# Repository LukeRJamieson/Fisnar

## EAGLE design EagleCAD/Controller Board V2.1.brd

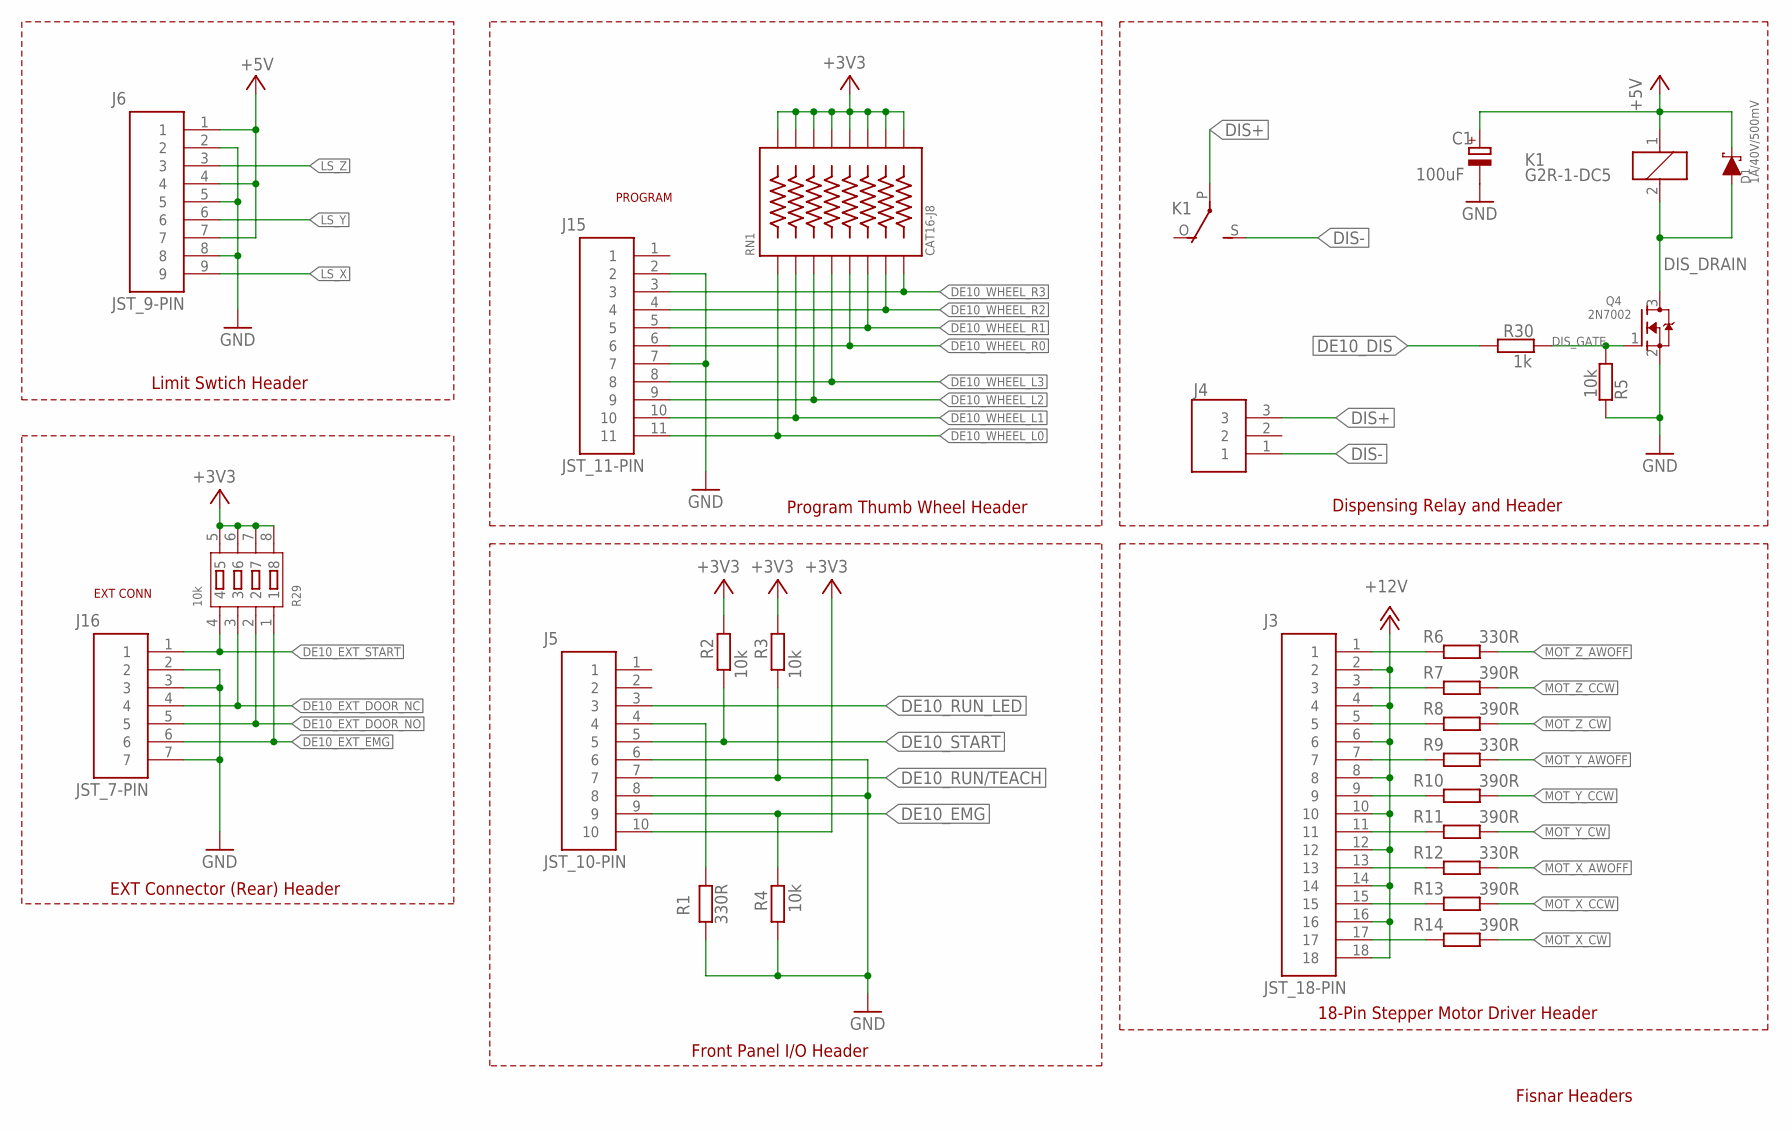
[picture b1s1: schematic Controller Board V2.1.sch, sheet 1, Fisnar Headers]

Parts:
C1: 100uF; 153CLV-0810
D1: 1A/40V/500mV; SMA-DIODE
J3: JST_18-PIN
J4: JST_3-PIN
J5: JST_10-PIN
J6: JST_9-PIN
J15: JST_11-PIN
J16: JST_7-PIN
K1: G2R-1-DC5; G2R
Q4: 2N7002; SOT23
R1, R6, R9, R12: 330R; R0805
R2, R3, R4, R5: 10k; R0805
R7, R8, R10, R11, R13, R14: 390R; R0805
R29: 10k; RA1206-8
R30: 1k; R0805
RN1: CAT16-J8; RN8

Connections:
+3V3: J5.10, R2.2, R3.2, R29.5, R29.6, R29.7, R29.8, RN1.2, RN1.4, RN1.6, RN1.8, RN1.10, RN1.12, RN1.14, RN1.16; also elsewhere on the board
+5V: C1.+, D1.C, J6.1, J6.4, J6.7, K1.1; also elsewhere on the board
+12V: J3.2, J3.4, J3.6, J3.8, J3.10, J3.12, J3.14, J3.16, J3.18; also elsewhere on the board
DE10_DIS: R30.2; also elsewhere on the board
DE10_EMG: J5.9, R4.2; also elsewhere on the board
DE10_EXT_DOOR_NC: J16.4, R29.3; also elsewhere on the board
DE10_EXT_DOOR_NO: J16.5, R29.2; also elsewhere on the board
DE10_EXT_EMG: J16.6, R29.1; also elsewhere on the board
DE10_EXT_START: J16.1, R29.4; also elsewhere on the board
DE10_RUN/TEACH: J5.7, R3.1; also elsewhere on the board
DE10_RUN_LED: J5.3; also elsewhere on the board
DE10_START: J5.5, R2.1; also elsewhere on the board
DE10_WHEEL_L0: J15.11, RN1.1; also elsewhere on the board
DE10_WHEEL_L1: J15.10, RN1.3; also elsewhere on the board
DE10_WHEEL_L2: J15.9, RN1.5; also elsewhere on the board
DE10_WHEEL_L3: J15.8, RN1.7; also elsewhere on the board
DE10_WHEEL_R0: J15.6, RN1.9; also elsewhere on the board
DE10_WHEEL_R1: J15.5, RN1.11; also elsewhere on the board
DE10_WHEEL_R2: J15.4, RN1.13; also elsewhere on the board
DE10_WHEEL_R3: J15.3, RN1.15; also elsewhere on the board
DIS+: J4.3, K1.P
DIS-: J4.1, K1.S
DIS_DRAIN: D1.A, K1.2, Q4.3 (D)
DIS_GATE: Q4.1 (G), R5.2, R30.1
GND: C1.-, J5.6, J5.8, J6.2, J6.5, J6.8, J15.2, J15.7, J16.2, J16.3, J16.7, Q4.2 (S), R1.2, R4.1, R5.1; also elsewhere on the board
LS_X: J6.9; also elsewhere on the board
LS_Y: J6.6; also elsewhere on the board
LS_Z: J6.3; also elsewhere on the board
MOT_X_AWOFF: R12.1; also elsewhere on the board
MOT_X_CCW: R13.1; also elsewhere on the board
MOT_X_CW: R14.1; also elsewhere on the board
MOT_Y_AWOFF: R9.1; also elsewhere on the board
MOT_Y_CCW: R10.1; also elsewhere on the board
MOT_Y_CW: R11.1; also elsewhere on the board
MOT_Z_AWOFF: R6.1; also elsewhere on the board
MOT_Z_CCW: R7.1; also elsewhere on the board
MOT_Z_CW: R8.1; also elsewhere on the board
RUN_LED_RES: J5.4, R1.1
X_AWOFF_NEG: J3.13, R12.2
X_CCW_NEG: J3.15, R13.2
X_CW_NEG: J3.17, R14.2
Y_AWOFF_NEG: J3.7, R9.2
Y_CCW_NEG: J3.9, R10.2
Y_CW_NEG: J3.11, R11.2
Z_AWOFF_NEG: J3.1, R6.2
Z_CCW_NEG: J3.3, R7.2
Z_CW_NEG: J3.5, R8.2

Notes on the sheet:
Fisnar Headers
EXT CONN
PROGRAM
18-Pin Stepper Motor Driver Header
Front Panel I/O Header
EXT Connector (Rear) Header
Limit Swtich Header
Program Thumb Wheel Header
Dispensing Relay and Header

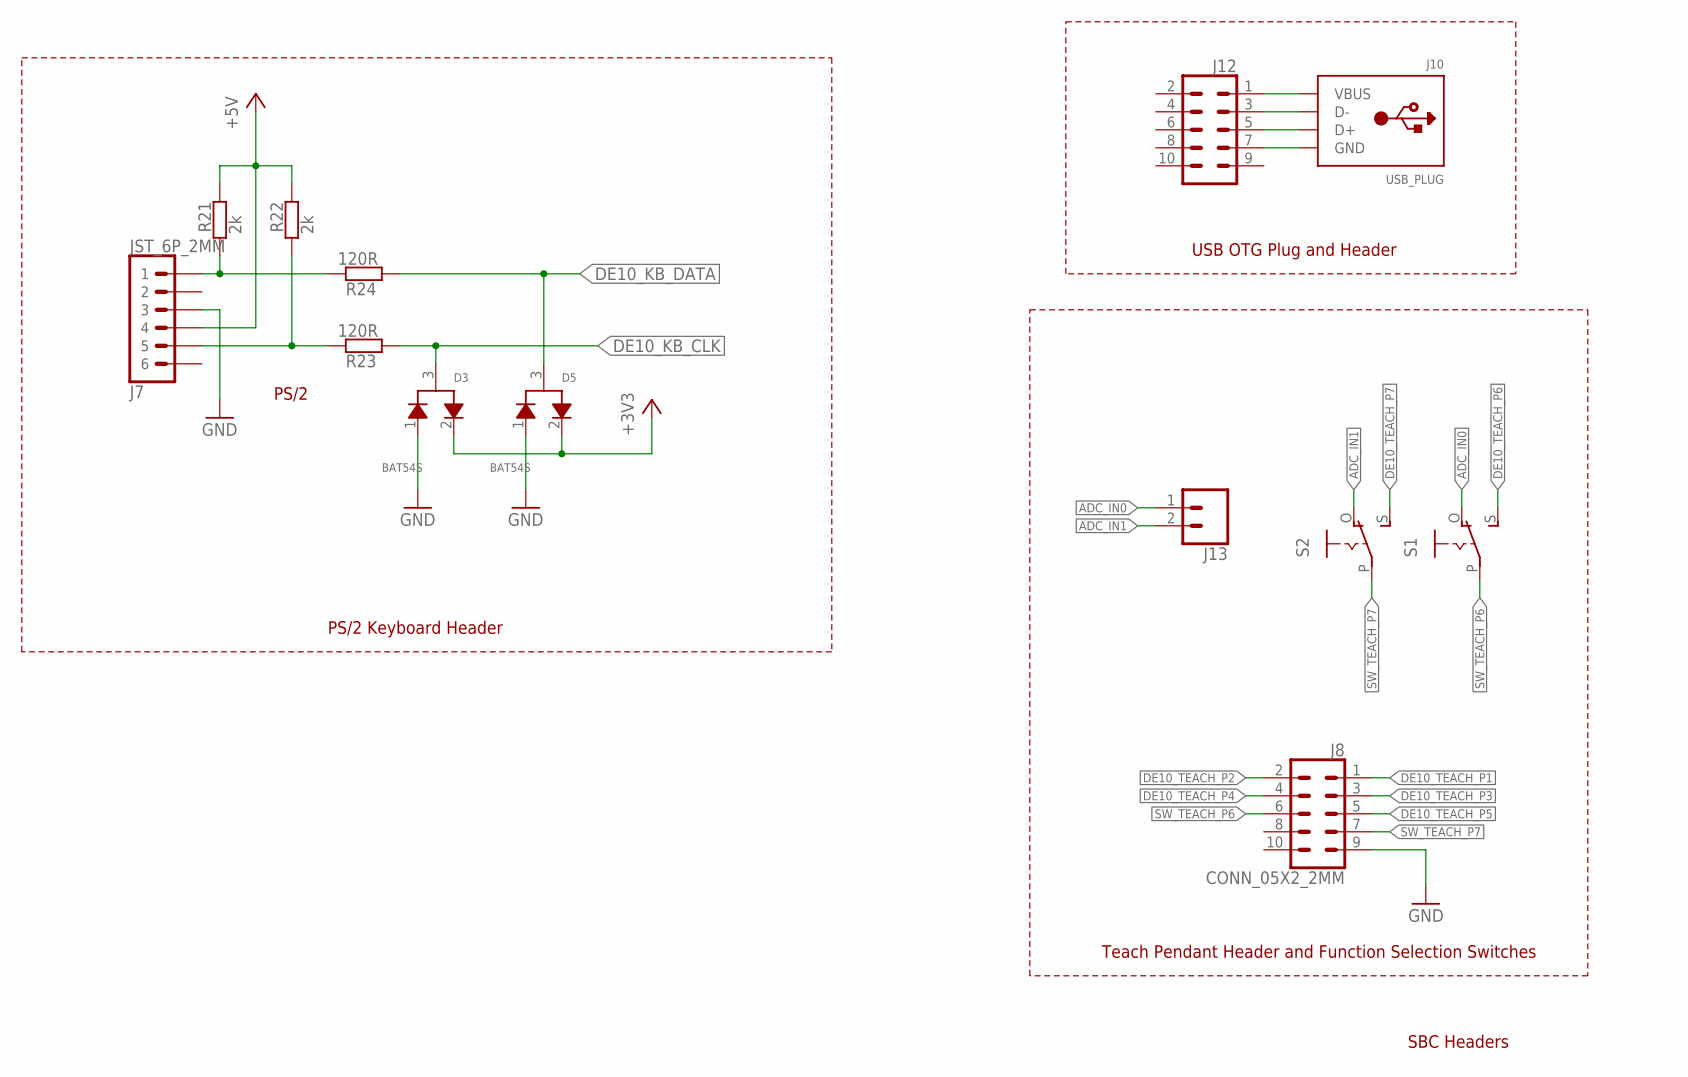
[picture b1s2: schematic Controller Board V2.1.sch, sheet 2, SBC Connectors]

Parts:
D3, D5: BAT54S; SOT23
J7: JST_6P_2MM
J8: CONN_05X2_2MM; 2X5-SHROUDED-2MM
J10: USB_PLUG
J12: CONN_05X2PTH; 2X5
J13: CONN_02; 1X02
R21, R22: 2k; R0805
R23, R24: 120R; R0805
S1, S2: EG1218S; EG1218

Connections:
+3V3: D3.2, D5.2; also elsewhere on the board
+5V: J7.P$4 (4), R21.2, R22.2; also elsewhere on the board
ADC_IN0: J13.1, S1.O
ADC_IN1: J13.2, S2.O
DE10_KB_CLK: D3.3, R23.1; also elsewhere on the board
DE10_KB_DATA: D5.3, R24.1; also elsewhere on the board
DE10_TEACH_P1: J8.1; also elsewhere on the board
DE10_TEACH_P2: J8.2; also elsewhere on the board
DE10_TEACH_P3: J8.3; also elsewhere on the board
DE10_TEACH_P4: J8.4; also elsewhere on the board
DE10_TEACH_P5: J8.5; also elsewhere on the board
DE10_TEACH_P6: S1.S; also elsewhere on the board
DE10_TEACH_P7: S2.S; also elsewhere on the board
GND: D3.1, D5.1, J7.P$3 (3), J8.9; also elsewhere on the board
OTG_D+: J10.D+, J12.5
OTG_D-: J10.D-, J12.3
OTG_GND: J10.USB_GND (GND), J12.7
OTG_VBUS: J10.VBUS, J12.1
PS2_KB_CLK: J7.P$5 (5), R22.1, R23.2
PS2_KB_DATA: J7.P$1 (1), R21.1, R24.2
SW_TEACH_P6: J8.6, S1.P
SW_TEACH_P7: J8.7, S2.P

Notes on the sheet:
PS/2
SBC Headers
PS/2 Keyboard Header
USB OTG Plug and Header
Teach Pendant Header and Function Selection Switches

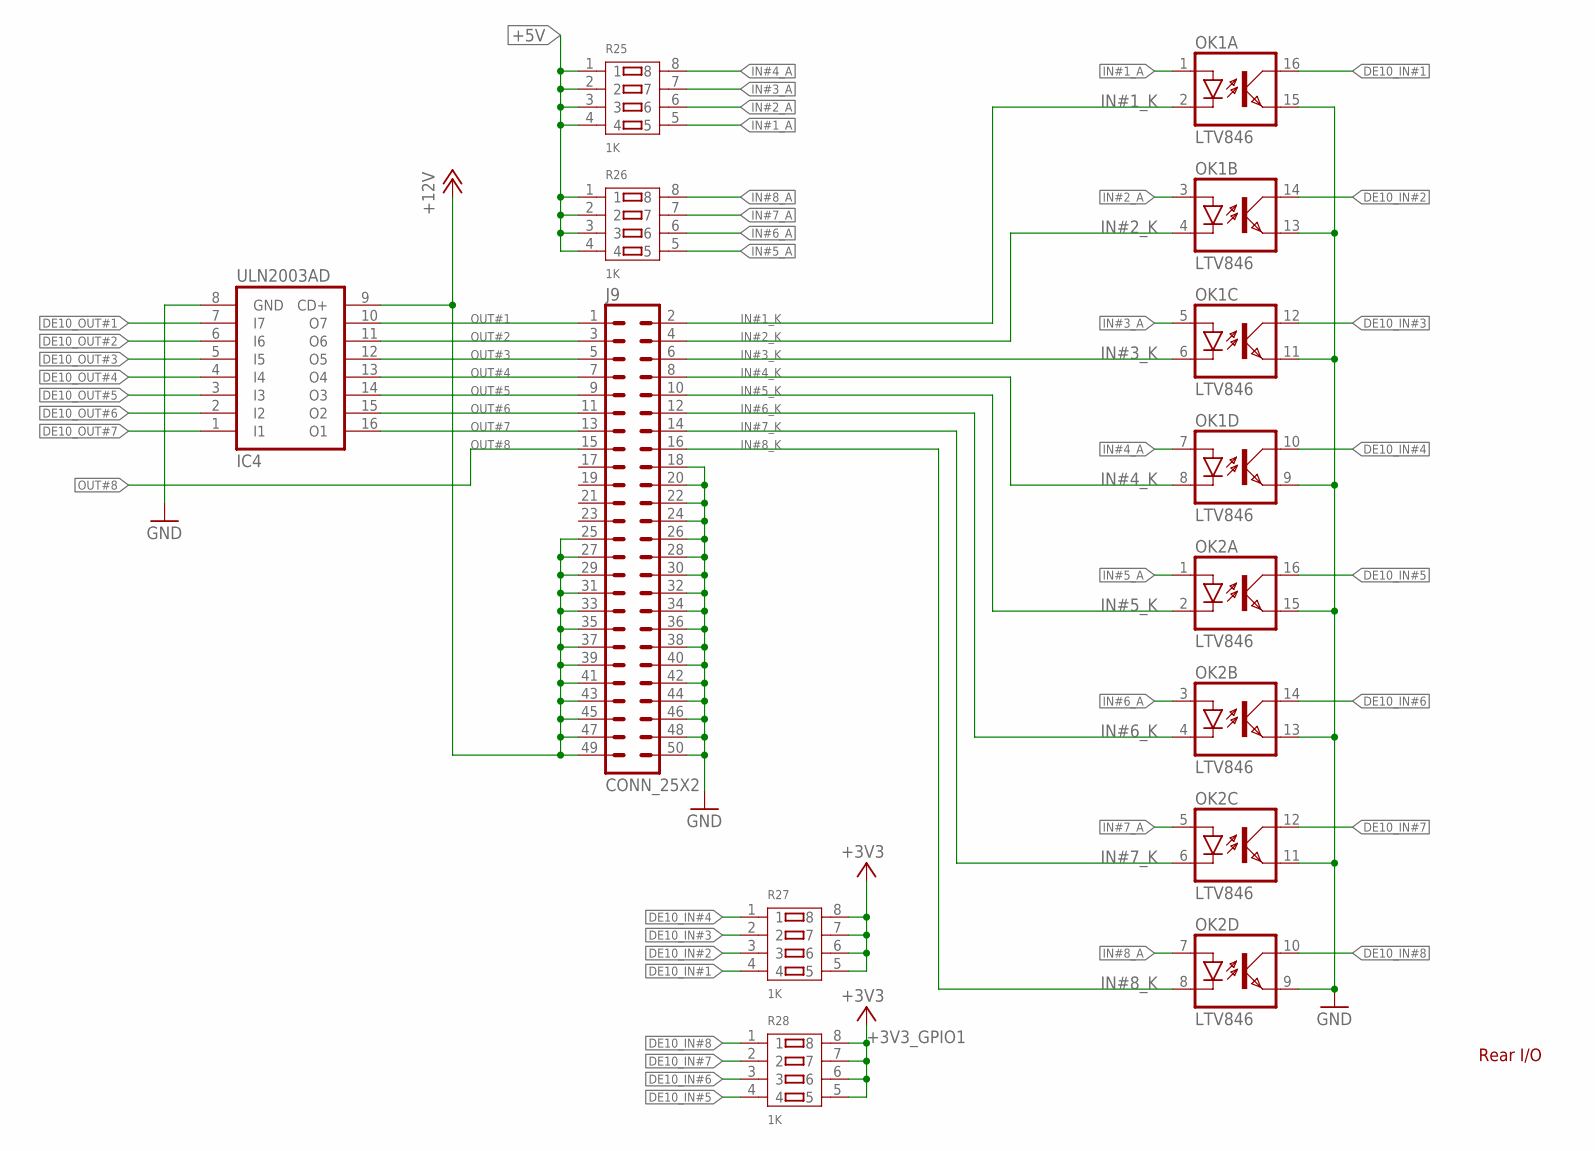
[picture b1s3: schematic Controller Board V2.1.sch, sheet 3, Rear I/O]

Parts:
IC4: ULN2003AD; SO16
J9: CONN_25X2; 2X25
OK1, OK2: LTV846; DIL8-SMD
R25, R26, R27, R28: 1K; RA1206-8

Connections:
+3V3: R27.5, R27.6, R27.7, R27.8; also elsewhere on the board
+3V3_GPIO1: R28.5, R28.6, R28.7, R28.8; also elsewhere on the board
+5V: R25.1, R25.2, R25.3, R25.4, R26.1, R26.2, R26.3, R26.4; also elsewhere on the board
+12V: IC4.9 (CD+), J9.25, J9.27, J9.29, J9.31, J9.33, J9.35, J9.37, J9.39, J9.41, J9.43, J9.45, J9.47, J9.49; also elsewhere on the board
DE10_IN#1: OK1.16 (COL), R27.4; also elsewhere on the board
DE10_IN#2: OK1.14 (COL), R27.3; also elsewhere on the board
DE10_IN#3: OK1.12 (COL), R27.2; also elsewhere on the board
DE10_IN#4: OK1.10 (COL), R27.1; also elsewhere on the board
DE10_IN#5: OK2.16 (COL), R28.4; also elsewhere on the board
DE10_IN#6: OK2.14 (COL), R28.3; also elsewhere on the board
DE10_IN#7: OK2.12 (COL), R28.2; also elsewhere on the board
DE10_IN#8: OK2.10 (COL), R28.1; also elsewhere on the board
DE10_OUT#1: IC4.7 (I7); also elsewhere on the board
DE10_OUT#2: IC4.6 (I6); also elsewhere on the board
DE10_OUT#3: IC4.5 (I5); also elsewhere on the board
DE10_OUT#4: IC4.4 (I4); also elsewhere on the board
DE10_OUT#5: IC4.3 (I3); also elsewhere on the board
DE10_OUT#6: IC4.2 (I2); also elsewhere on the board
DE10_OUT#7: IC4.1 (I1); also elsewhere on the board
GND: IC4.8 (GND), J9.18, J9.20, J9.22, J9.24, J9.26, J9.28, J9.30, J9.32, J9.34, J9.36, J9.38, J9.40, J9.42, J9.44, J9.46, J9.48, J9.50, OK1.9 (EMIT), OK1.11 (EMIT), OK1.13 (EMIT), OK1.15 (EMIT), OK2.9 (EMIT), OK2.11 (EMIT), OK2.13 (EMIT), OK2.15 (EMIT); also elsewhere on the board
IN#1_A: OK1.1 (A), R25.5
IN#1_K: J9.2, OK1.2 (C)
IN#2_A: OK1.3 (A), R25.6
IN#2_K: J9.4, OK1.4 (C)
IN#3_A: OK1.5 (A), R25.7
IN#3_K: J9.6, OK1.6 (C)
IN#4_A: OK1.7 (A), R25.8
IN#4_K: J9.8, OK1.8 (C)
IN#5_A: OK2.1 (A), R26.5
IN#5_K: J9.10, OK2.2 (C)
IN#6_A: OK2.3 (A), R26.6
IN#6_K: J9.12, OK2.4 (C)
IN#7_A: OK2.5 (A), R26.7
IN#7_K: J9.14, OK2.6 (C)
IN#8_A: OK2.7 (A), R26.8
IN#8_K: J9.16, OK2.8 (C)
OUT#1: IC4.10 (O7), J9.1
OUT#2: IC4.11 (O6), J9.3
OUT#3: IC4.12 (O5), J9.5
OUT#4: IC4.13 (O4), J9.7
OUT#5: IC4.14 (O3), J9.9
OUT#6: IC4.15 (O2), J9.11
OUT#7: IC4.16 (O1), J9.13
OUT#8: J9.15; also elsewhere on the board

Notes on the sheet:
Rear I/O

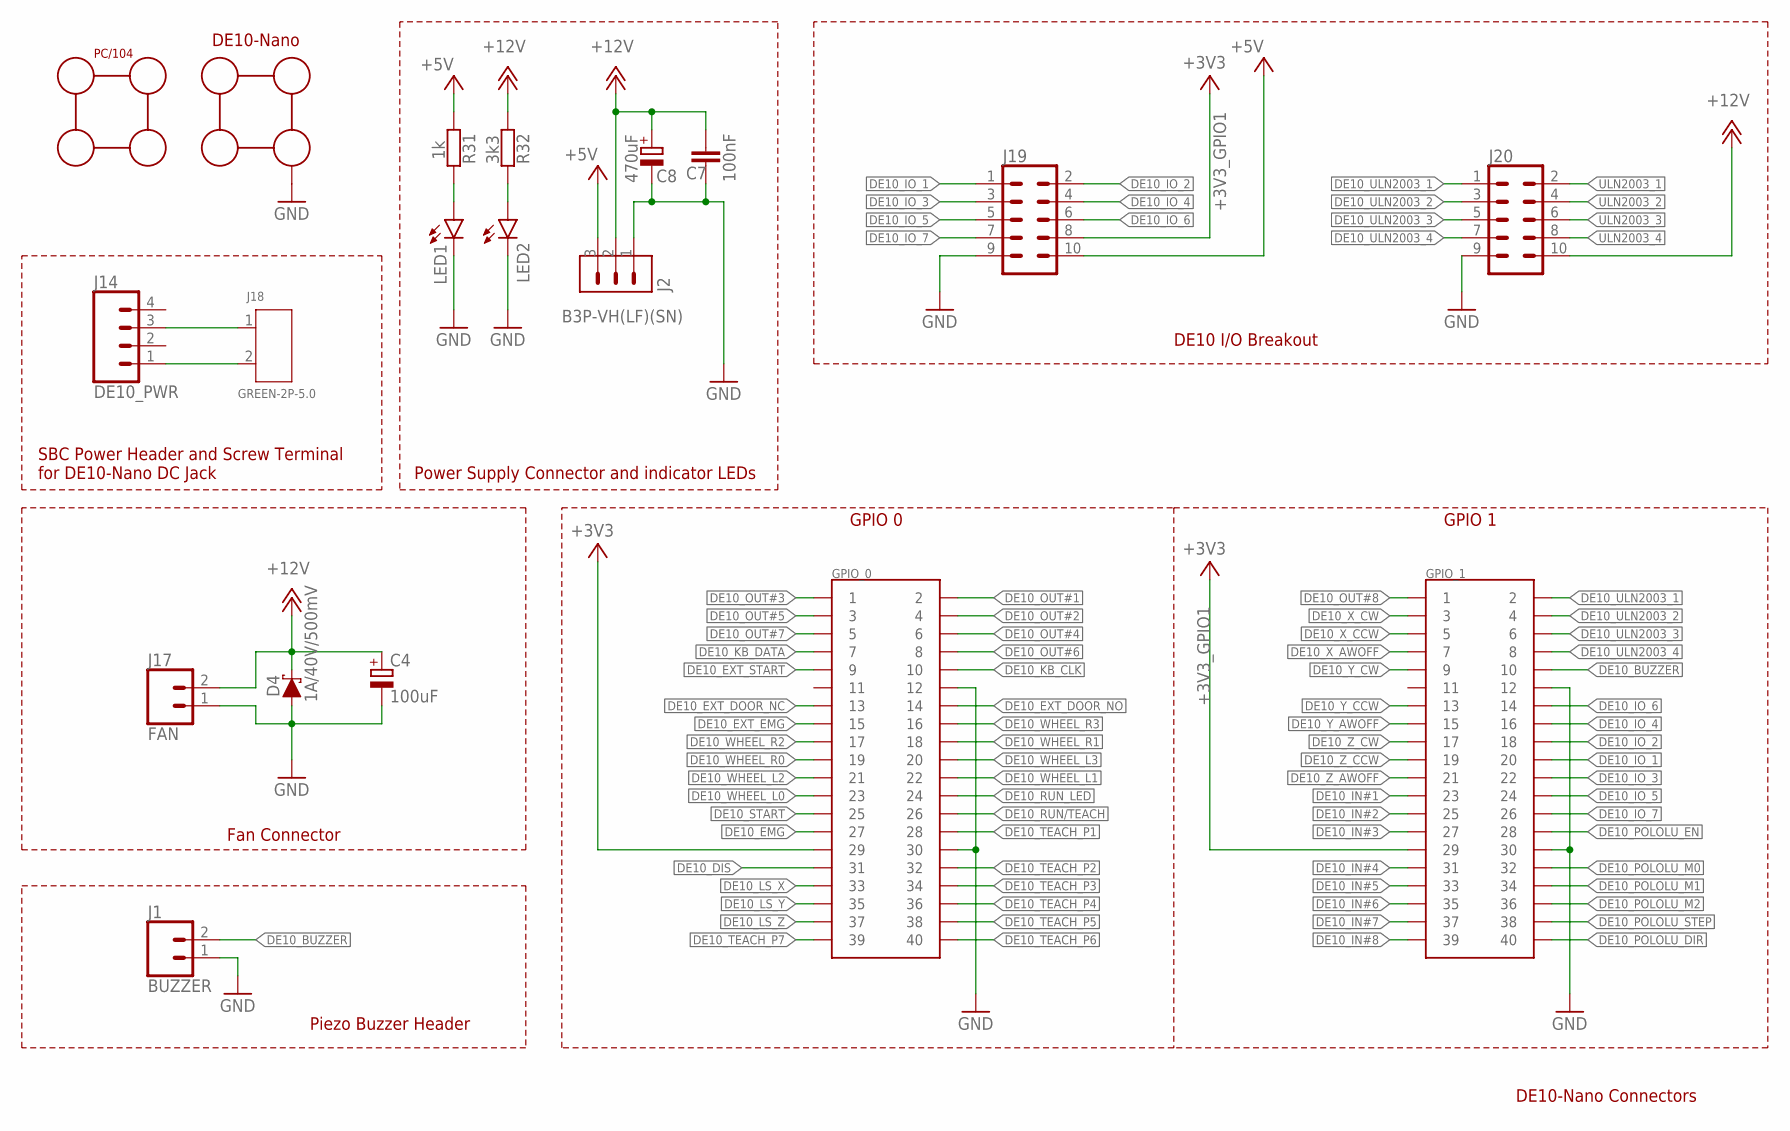
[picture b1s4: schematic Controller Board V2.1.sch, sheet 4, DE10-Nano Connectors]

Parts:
C4: 100uF; 153CLV-0810
C7: 100nF; C0805
C8: 470uF; 153CLV-0810
D4: 1A/40V/500mV; SMA-DIODE
DE1: DE10_FOOTPRINT
J1: BUZZER; 1X02
J2: B3P-VH(LF)(SN); HDR-03
J14: DE10_PWR; 1X04_NO_SILK
J17: FAN; 1X02
J18: GREEN-2P-5.0; H2-5.0-10.5X8.0MM
J19, J20: CONN_05X2PTH; 2X5
LED1, LED2: LEDCHIP-LED0805; CHIP-LED0805
R31: 1k; R0805
R32: 3k3; R0805
U$1: PC104_FOOTPRINT

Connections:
+3V3: DE1.GPIO_0_29 (29); also elsewhere on the board
+3V3_GPIO1: DE1.GPIO_1_29 (29), J19.8; also elsewhere on the board
+5V: J2.3, J19.10, R31.1; also elsewhere on the board
+12V: C4.+, C7.1, C8.+, D4.C, J2.2, J17.2, J20.10, R32.1; also elsewhere on the board
DE10_BUZZER: DE1.GPIO_1_10 (10), J1.2
DE10_DCJACK_5V: J14.1, J18.2
DE10_DCJACK_GND: J14.3, J18.1
DE10_DIS: DE1.GPIO_0_31 (31); also elsewhere on the board
DE10_EMG: DE1.GPIO_0_27 (27); also elsewhere on the board
DE10_EXT_DOOR_NC: DE1.GPIO_0_13 (13); also elsewhere on the board
DE10_EXT_DOOR_NO: DE1.GPIO_0_14 (14); also elsewhere on the board
DE10_EXT_EMG: DE1.GPIO_0_15 (15); also elsewhere on the board
DE10_EXT_START: DE1.GPIO_0_9 (9); also elsewhere on the board
DE10_IN#1: DE1.GPIO_1_23 (23); also elsewhere on the board
DE10_IN#2: DE1.GPIO_1_25 (25); also elsewhere on the board
DE10_IN#3: DE1.GPIO_1_27 (27); also elsewhere on the board
DE10_IN#4: DE1.GPIO_1_31 (31); also elsewhere on the board
DE10_IN#5: DE1.GPIO_1_33 (33); also elsewhere on the board
DE10_IN#6: DE1.GPIO_1_35 (35); also elsewhere on the board
DE10_IN#7: DE1.GPIO_1_37 (37); also elsewhere on the board
DE10_IN#8: DE1.GPIO_1_39 (39); also elsewhere on the board
DE10_IO_1: DE1.GPIO_1_20 (20), J19.1
DE10_IO_2: DE1.GPIO_1_18 (18), J19.2
DE10_IO_3: DE1.GPIO_1_22 (22), J19.3
DE10_IO_4: DE1.GPIO_1_16 (16), J19.4
DE10_IO_5: DE1.GPIO_1_24 (24), J19.5
DE10_IO_6: DE1.GPIO_1_14 (14), J19.6
DE10_IO_7: DE1.GPIO_1_26 (26), J19.7
DE10_KB_CLK: DE1.GPIO_0_10 (10); also elsewhere on the board
DE10_KB_DATA: DE1.GPIO_0_7 (7); also elsewhere on the board
DE10_LS_X: DE1.GPIO_0_33 (33); also elsewhere on the board
DE10_LS_Y: DE1.GPIO_0_35 (35); also elsewhere on the board
DE10_LS_Z: DE1.GPIO_0_37 (37); also elsewhere on the board
DE10_OUT#1: DE1.GPIO_0_2 (2); also elsewhere on the board
DE10_OUT#2: DE1.GPIO_0_4 (4); also elsewhere on the board
DE10_OUT#3: DE1.GPIO_0_1 (1); also elsewhere on the board
DE10_OUT#4: DE1.GPIO_0_6 (6); also elsewhere on the board
DE10_OUT#5: DE1.GPIO_0_3 (3); also elsewhere on the board
DE10_OUT#6: DE1.GPIO_0_8 (8); also elsewhere on the board
DE10_OUT#7: DE1.GPIO_0_5 (5); also elsewhere on the board
DE10_OUT#8: DE1.GPIO_1_1 (1); also elsewhere on the board
DE10_POLOLU_DIR: DE1.GPIO_1_40 (40); also elsewhere on the board
DE10_POLOLU_EN: DE1.GPIO_1_28 (28); also elsewhere on the board
DE10_POLOLU_M0: DE1.GPIO_1_32 (32); also elsewhere on the board
DE10_POLOLU_M1: DE1.GPIO_1_34 (34); also elsewhere on the board
DE10_POLOLU_M2: DE1.GPIO_1_36 (36); also elsewhere on the board
DE10_POLOLU_STEP: DE1.GPIO_1_38 (38); also elsewhere on the board
DE10_RUN/TEACH: DE1.GPIO_0_26 (26); also elsewhere on the board
DE10_RUN_LED: DE1.GPIO_0_24 (24); also elsewhere on the board
DE10_START: DE1.GPIO_0_25 (25); also elsewhere on the board
DE10_TEACH_P1: DE1.GPIO_0_28 (28); also elsewhere on the board
DE10_TEACH_P2: DE1.GPIO_0_32 (32); also elsewhere on the board
DE10_TEACH_P3: DE1.GPIO_0_34 (34); also elsewhere on the board
DE10_TEACH_P4: DE1.GPIO_0_36 (36); also elsewhere on the board
DE10_TEACH_P5: DE1.GPIO_0_38 (38); also elsewhere on the board
DE10_TEACH_P6: DE1.GPIO_0_40 (40); also elsewhere on the board
DE10_TEACH_P7: DE1.GPIO_0_39 (39); also elsewhere on the board
DE10_ULN2003_1: DE1.GPIO_1_2 (2), J20.1; also elsewhere on the board
DE10_ULN2003_2: DE1.GPIO_1_4 (4), J20.3; also elsewhere on the board
DE10_ULN2003_3: DE1.GPIO_1_6 (6), J20.5; also elsewhere on the board
DE10_ULN2003_4: DE1.GPIO_1_8 (8), J20.7; also elsewhere on the board
DE10_WHEEL_L0: DE1.GPIO_0_23 (23); also elsewhere on the board
DE10_WHEEL_L1: DE1.GPIO_0_22 (22); also elsewhere on the board
DE10_WHEEL_L2: DE1.GPIO_0_21 (21); also elsewhere on the board
DE10_WHEEL_L3: DE1.GPIO_0_20 (20); also elsewhere on the board
DE10_WHEEL_R0: DE1.GPIO_0_19 (19); also elsewhere on the board
DE10_WHEEL_R1: DE1.GPIO_0_18 (18); also elsewhere on the board
DE10_WHEEL_R2: DE1.GPIO_0_17 (17); also elsewhere on the board
DE10_WHEEL_R3: DE1.GPIO_0_16 (16); also elsewhere on the board
DE10_X_AWOFF: DE1.GPIO_1_7 (7); also elsewhere on the board
DE10_X_CCW: DE1.GPIO_1_5 (5); also elsewhere on the board
DE10_X_CW: DE1.GPIO_1_3 (3); also elsewhere on the board
DE10_Y_AWOFF: DE1.GPIO_1_15 (15); also elsewhere on the board
DE10_Y_CCW: DE1.GPIO_1_13 (13); also elsewhere on the board
DE10_Y_CW: DE1.GPIO_1_9 (9); also elsewhere on the board
DE10_Z_AWOFF: DE1.GPIO_1_21 (21); also elsewhere on the board
DE10_Z_CCW: DE1.GPIO_1_19 (19); also elsewhere on the board
DE10_Z_CW: DE1.GPIO_1_17 (17); also elsewhere on the board
GND: C4.-, C7.2, C8.-, D4.A, DE1.GPIO_0_12 (12), DE1.GPIO_0_30 (30), DE1.GPIO_1_12 (12), DE1.GPIO_1_30 (30), DE1.P$1, DE1.P$2, DE1.P$3, DE1.P$4, J1.1, J2.1, J17.1, J19.9, J20.9, LED1.C, LED2.C; also elsewhere on the board
unnamed: LED1.A, R31.2
unnamed: LED2.A, R32.2
ULN2003_1: J20.2; also elsewhere on the board
ULN2003_2: J20.4; also elsewhere on the board
ULN2003_3: J20.6; also elsewhere on the board
ULN2003_4: J20.8; also elsewhere on the board

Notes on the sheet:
DE10-Nano Connectors
DE10 I/O Breakout
GPIO 0
GPIO 1
Power Supply Connector and indicator LEDs
SBC Power Header and Screw Terminal for DE10-Nano DC Jack
Fan Connector
Piezo Buzzer Header

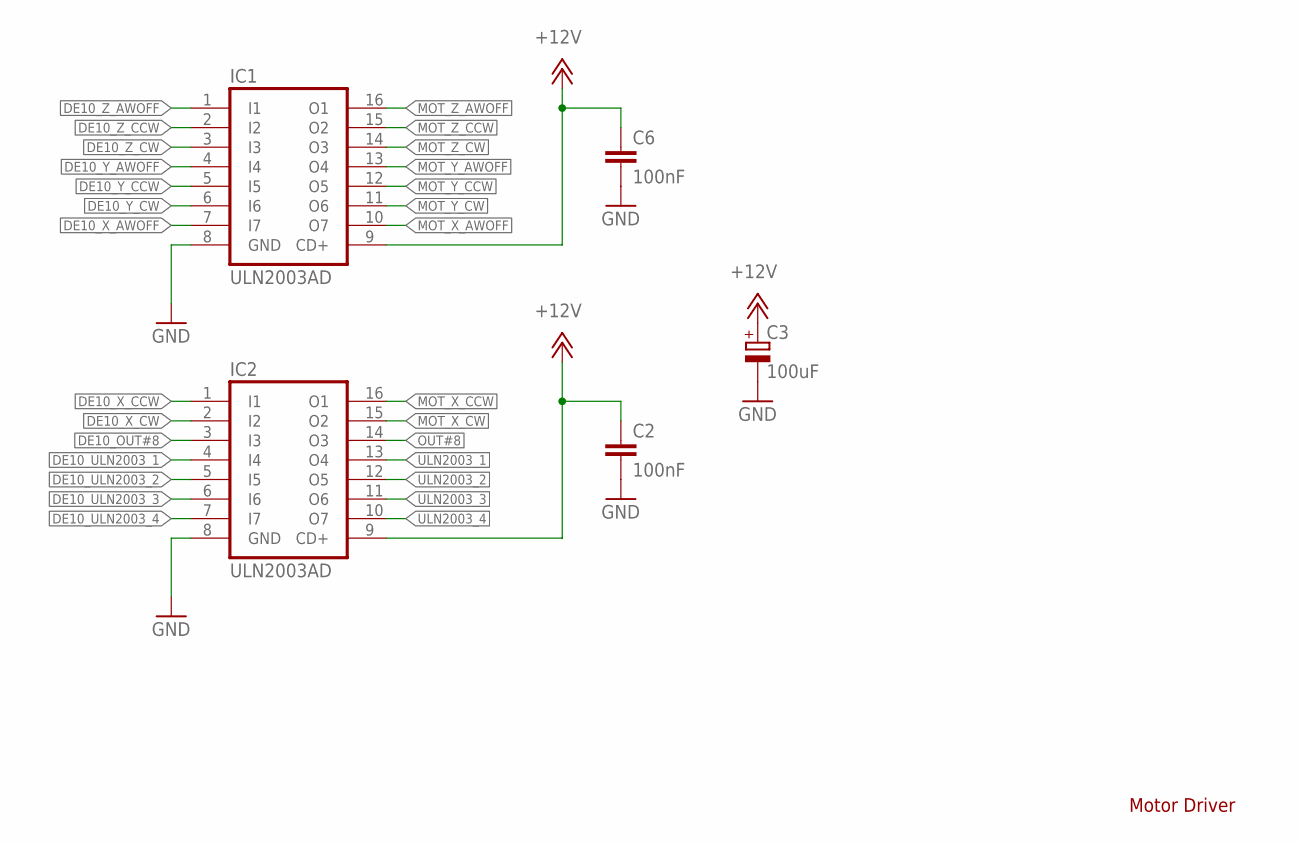
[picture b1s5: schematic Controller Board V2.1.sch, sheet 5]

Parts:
C2, C6: 100nF; C0805
C3: 100uF; 153CLV-0810
IC1, IC2: ULN2003AD; SO16

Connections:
+12V: C2.1, C3.+, C6.1, IC1.9 (CD+), IC2.9 (CD+); also elsewhere on the board
DE10_OUT#8: IC2.3 (I3); also elsewhere on the board
DE10_ULN2003_1: IC2.4 (I4); also elsewhere on the board
DE10_ULN2003_2: IC2.5 (I5); also elsewhere on the board
DE10_ULN2003_3: IC2.6 (I6); also elsewhere on the board
DE10_ULN2003_4: IC2.7 (I7); also elsewhere on the board
DE10_X_AWOFF: IC1.7 (I7); also elsewhere on the board
DE10_X_CCW: IC2.1 (I1); also elsewhere on the board
DE10_X_CW: IC2.2 (I2); also elsewhere on the board
DE10_Y_AWOFF: IC1.4 (I4); also elsewhere on the board
DE10_Y_CCW: IC1.5 (I5); also elsewhere on the board
DE10_Y_CW: IC1.6 (I6); also elsewhere on the board
DE10_Z_AWOFF: IC1.1 (I1); also elsewhere on the board
DE10_Z_CCW: IC1.2 (I2); also elsewhere on the board
DE10_Z_CW: IC1.3 (I3); also elsewhere on the board
GND: C2.2, C3.-, C6.2, IC1.8 (GND), IC2.8 (GND); also elsewhere on the board
MOT_X_AWOFF: IC1.10 (O7); also elsewhere on the board
MOT_X_CCW: IC2.16 (O1); also elsewhere on the board
MOT_X_CW: IC2.15 (O2); also elsewhere on the board
MOT_Y_AWOFF: IC1.13 (O4); also elsewhere on the board
MOT_Y_CCW: IC1.12 (O5); also elsewhere on the board
MOT_Y_CW: IC1.11 (O6); also elsewhere on the board
MOT_Z_AWOFF: IC1.16 (O1); also elsewhere on the board
MOT_Z_CCW: IC1.15 (O2); also elsewhere on the board
MOT_Z_CW: IC1.14 (O3); also elsewhere on the board
OUT#8: IC2.14 (O3); also elsewhere on the board
ULN2003_1: IC2.13 (O4); also elsewhere on the board
ULN2003_2: IC2.12 (O5); also elsewhere on the board
ULN2003_3: IC2.11 (O6); also elsewhere on the board
ULN2003_4: IC2.10 (O7); also elsewhere on the board

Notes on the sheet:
Motor Driver

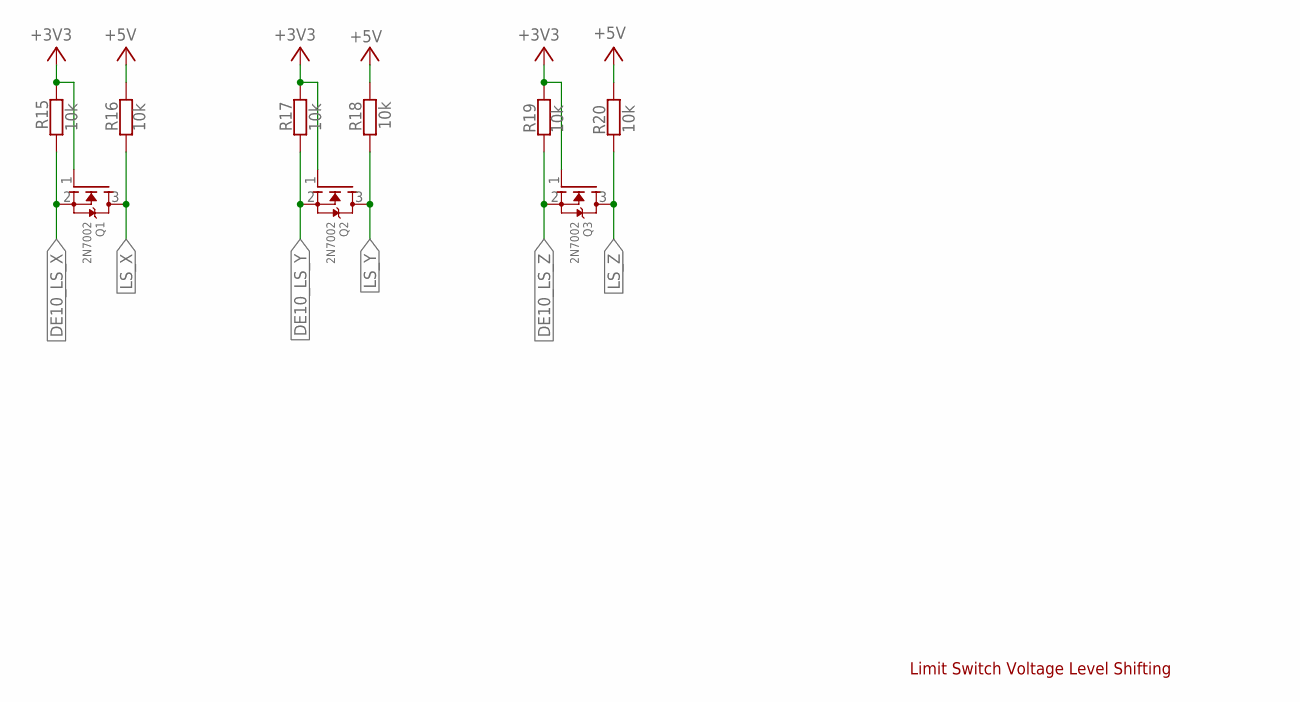
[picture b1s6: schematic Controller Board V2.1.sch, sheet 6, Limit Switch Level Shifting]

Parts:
Q1, Q2, Q3: 2N7002; SOT23
R15, R16, R17, R18, R19, R20: 10k; R0805

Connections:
+3V3: Q1.1 (G), Q2.1 (G), Q3.1 (G), R15.2, R17.2, R19.2; also elsewhere on the board
+5V: R16.2, R18.2, R20.2; also elsewhere on the board
DE10_LS_X: Q1.2 (S), R15.1; also elsewhere on the board
DE10_LS_Y: Q2.2 (S), R17.1; also elsewhere on the board
DE10_LS_Z: Q3.2 (S), R19.1; also elsewhere on the board
LS_X: Q1.3 (D), R16.1; also elsewhere on the board
LS_Y: Q2.3 (D), R18.1; also elsewhere on the board
LS_Z: Q3.3 (D), R20.1; also elsewhere on the board

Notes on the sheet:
Limit Switch Voltage Level Shifting

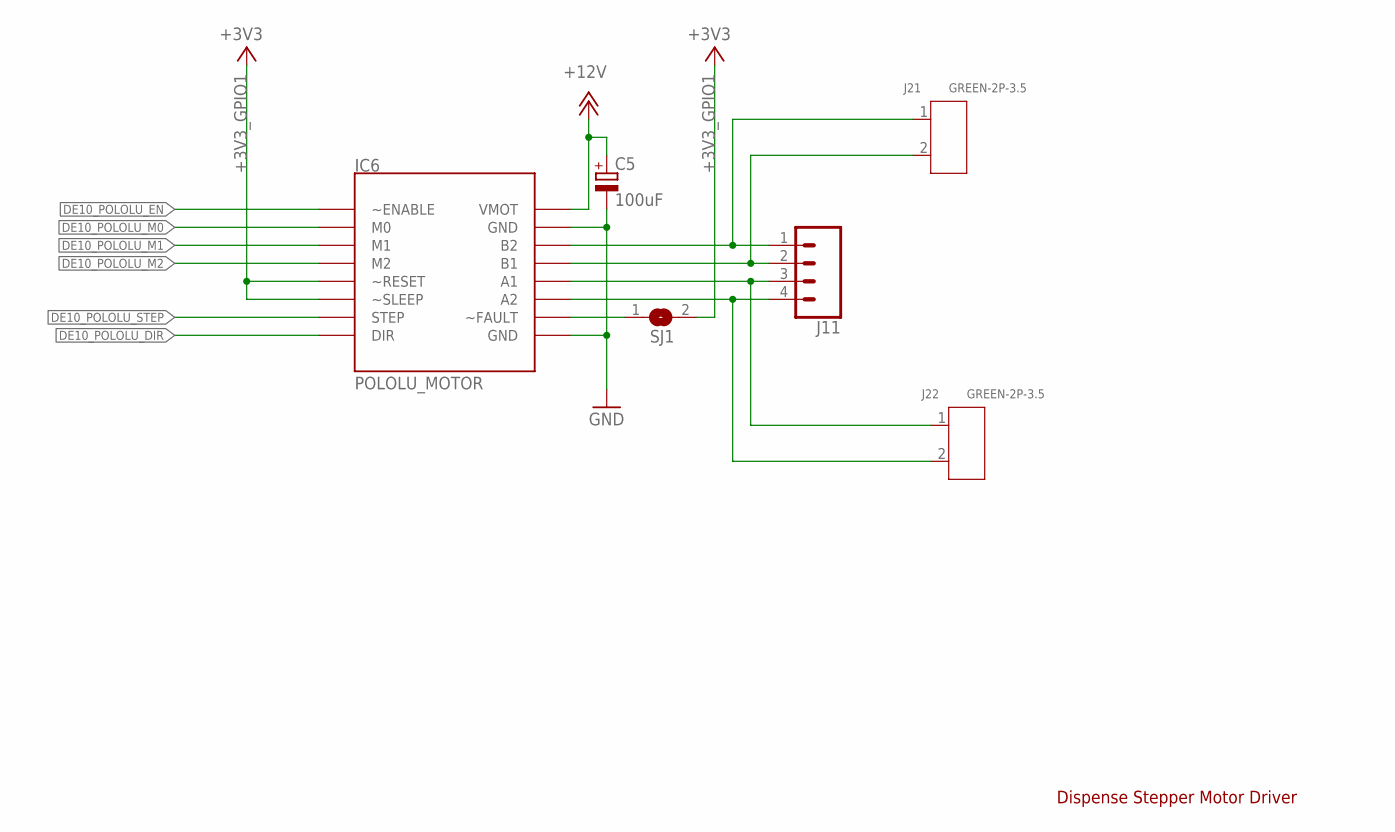
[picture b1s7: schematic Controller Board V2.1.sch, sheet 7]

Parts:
C5: 100uF; 153CLV-0810
IC6: POLOLU_MOTOR
J11: CONN_04; 1X04
J21, J22: GREEN-2P-3.5; H2-3.5-7.0X7.0MM
SJ1: SJ

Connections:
+3V3_GPIO1: IC6.~RESET, IC6.~SLEEP, SJ1.2; also elsewhere on the board
+12V: C5.+, IC6.VMOT; also elsewhere on the board
A1: IC6.A1, J11.3, J22.1
A2: IC6.A2, J11.4, J22.2
B1: IC6.B1, J11.2, J21.2
B2: IC6.B2, J11.1, J21.1
DE10_POLOLU_DIR: IC6.DIR; also elsewhere on the board
DE10_POLOLU_EN: IC6.~ENABLE; also elsewhere on the board
DE10_POLOLU_M0: IC6.M0; also elsewhere on the board
DE10_POLOLU_M1: IC6.M1; also elsewhere on the board
DE10_POLOLU_M2: IC6.M2; also elsewhere on the board
DE10_POLOLU_STEP: IC6.STEP; also elsewhere on the board
GND: C5.-, IC6.GND@0 (GND), IC6.GND@1 (GND); also elsewhere on the board
STEPPER_FAULT: IC6.~FAULT, SJ1.1

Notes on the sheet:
Dispense Stepper Motor Driver

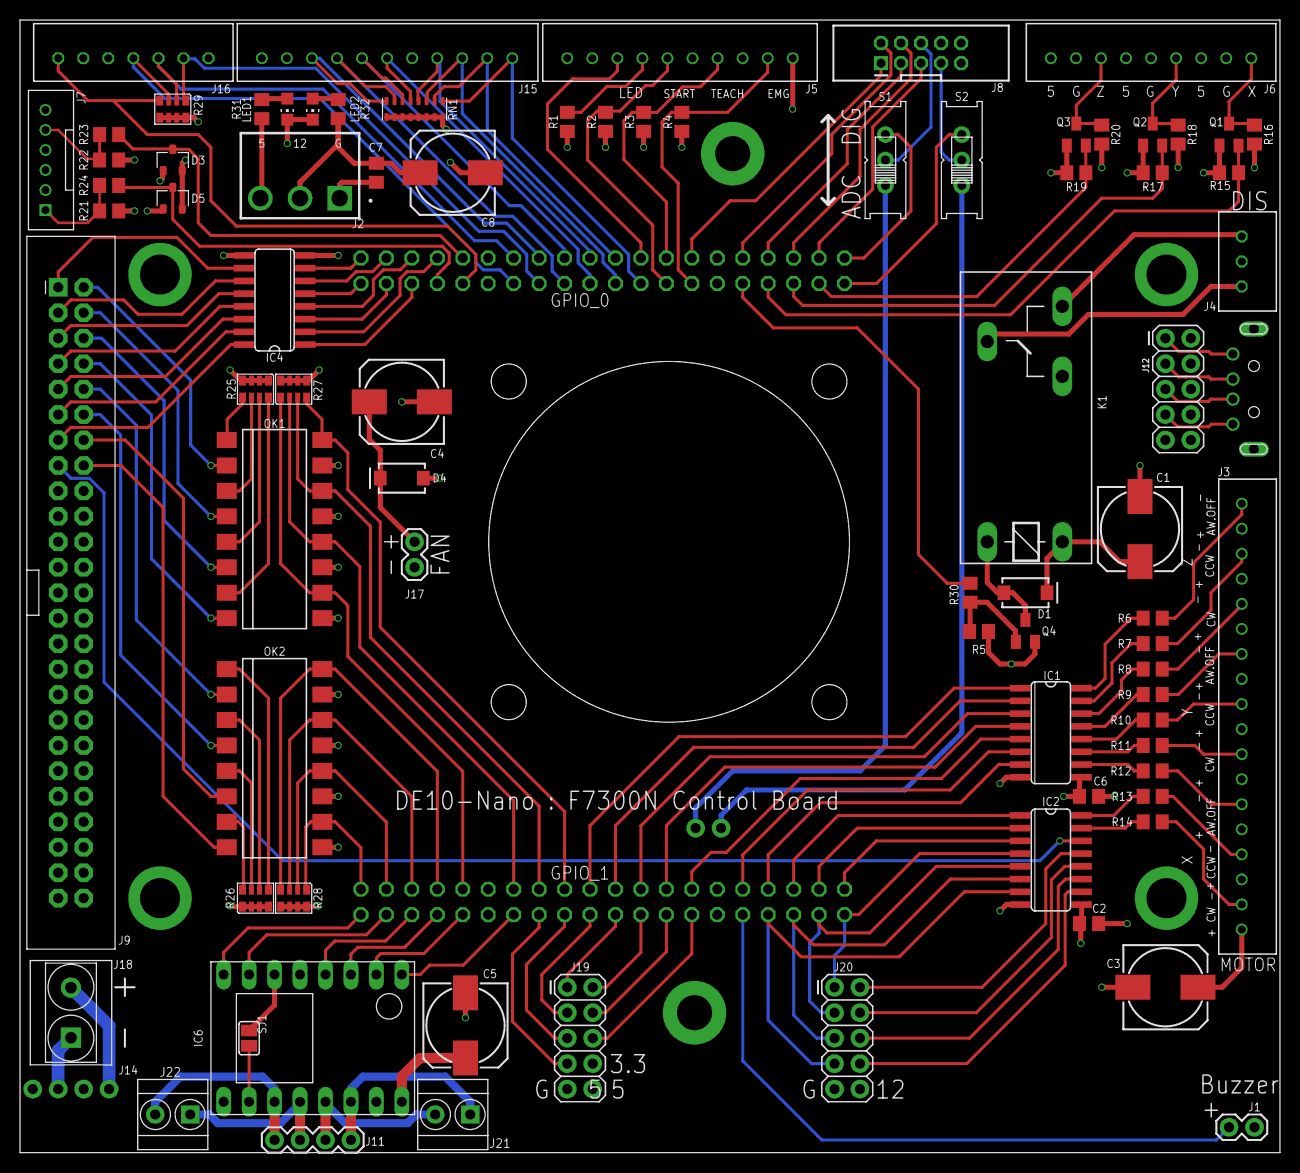
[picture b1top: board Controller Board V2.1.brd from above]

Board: 4 copper layers, 125.7 x 113.0 mm, 86 parts (1 on the bottom side), 150 nets.

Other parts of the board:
U$2: 40MM-FAN

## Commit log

2022-07-05 Create transform.c
    Function to perform translation and rotation transforms.
    Reference point is the location of the first fiducial referred to the Fisnar origin.
    Target point is the Gerber solder paste coordinate.
2022-07-05 Update transform.c
    Comments added for clarity
2022-07-06 Verilog Example Files
2022-07-06 Motor Control
2022-07-06 Motor Control Project Folder
2022-07-06 Removed unnecessary files
2022-08-07 Motor Control v2
2022-10-21 EagleCAD Files
2022-10-21 Added 3D Prints
2022-10-21 FisnarControl Library
2022-10-21 removed files
2022-10-21 Quartus Project
2022-10-23 Dispensing State Machine Example
    Contains Position Correction Algorithm
2022-10-23 Plot Rendered

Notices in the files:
parts and their libraries:
SparkFun-Connectors: Licensing: Creative Commons ShareAlike 4.0 International - https://creativecommons.org/licenses/by-sa/4.0
